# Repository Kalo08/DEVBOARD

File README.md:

# DEVBOARD

A custom devboard I made as a part of PROTOTYPE for HackClub.

Here are the parts I'm using,

1. USB-C port
2. Flash Memory
3. Crystal Oscillator
4. 1/0 Headers
5. RP2040
6. RGB Light
7. Custom Silk Screen

Rerouting, Adding details, and Ordering
I moved many of the routes to eliminate most of the warnings on my PCB and did extensive research on each error that appeared. I added a detail using the image converter, generated the Gerber and CSV files, uploaded them to JLCPCB, and started the ordering process. I had to change some parts because of what they had in stock, but my research says they should be equivalent.

-----------------------------------------------------------------------------------------------------------------------------------------------------------------------------------------------------------------------------------------------------------

Fixed the ts PCB and recreated it twice
Thanks to some hard drive issues, my KiCAD wasn't saving. So I re-created the whole thing, turned off my PC, then the next day logged on to finish it, and it was gone AGAIN! I replaced my hard drive, and KiCAD is working now. Thanks to that, I finally finished creating this PCB, and there aren't any errors. Now I get to add art to it!

With this newest iteration, I moved and changed many components after redoing this project twice, so I could route it as quickly as possible. It's safe to say I'm comfortable with KiCAD after this wholeexperiencee

-----------------------------------------------------------------------------------------------------------------------------------------------------------------------------------------------------------------------------------------------------------

created and routed the PCB
I placed all the electronics and routed them according to the schematic. Next, I'll test whether the PCB is functional and add art to it. I'll have to give it some thought, though. I've got some ideas for the art I'll add. And of course, Hack Club is gonna be one of said things.

-----------------------------------------------------------------------------------------------------------------------------------------------------------------------------------------------------------------------------------------------------------

Created Schematic
Just finished creating the schematic for the Dev Board. I followed the guide step by step and reviewed it for the finished product. Now I'm ready to move on to creating the PCB. I'm starting to dread the routing part though...

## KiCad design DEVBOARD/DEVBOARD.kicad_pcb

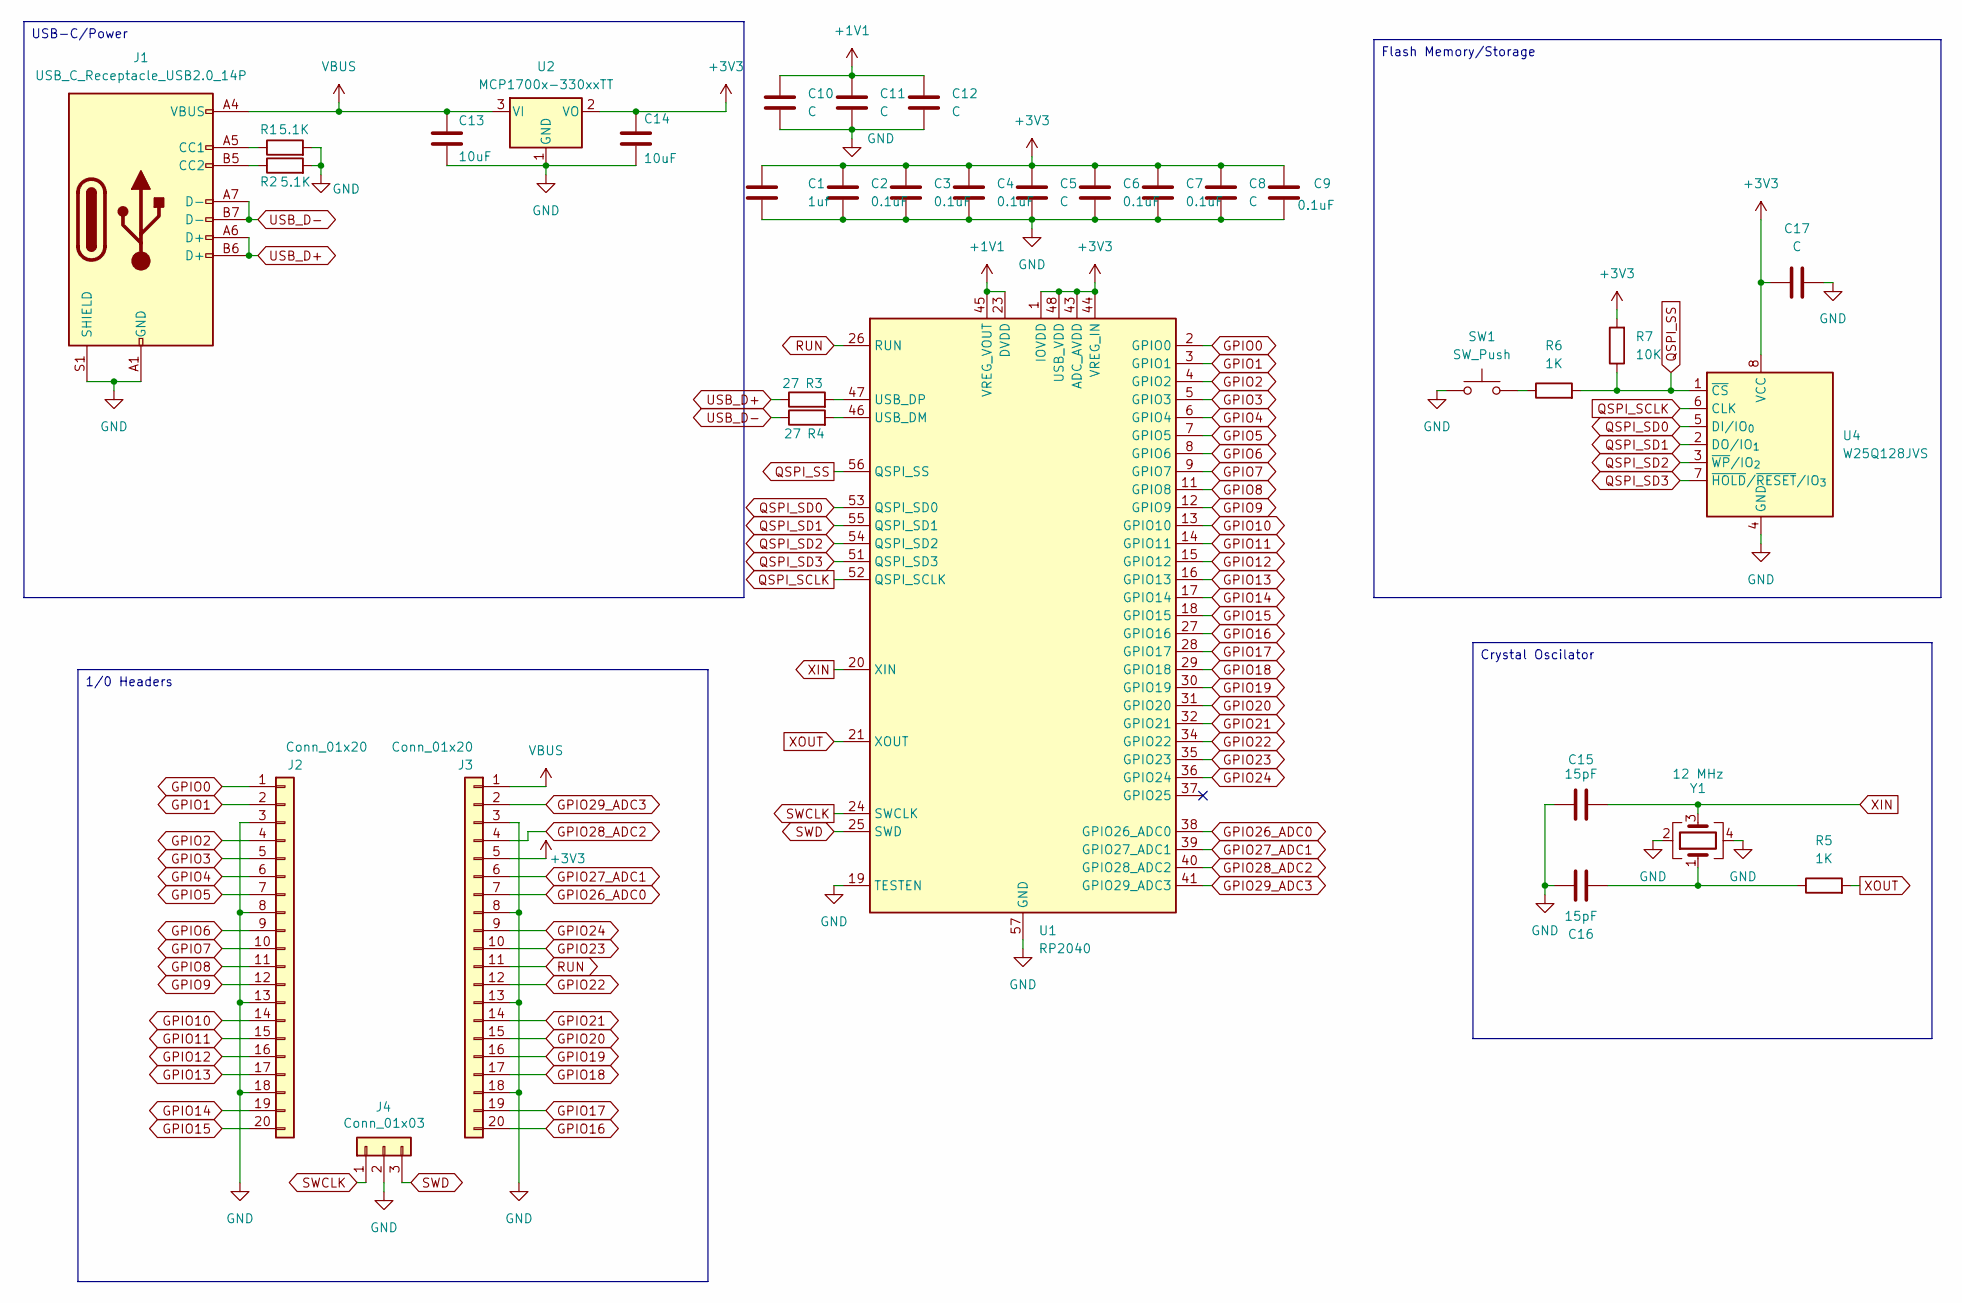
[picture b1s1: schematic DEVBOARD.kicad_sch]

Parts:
C1: 1uf; C_0402_1005Metric
C2, C3, C4, C6, C7, C9: 0.1uF; C_0402_1005Metric
C5, C8, C10, C11, C12, C17: C; C_0402_1005Metric
C13, C14: 10uF; C_0603_1608Metric
C15, C16: 15pF; C_0402_1005Metric
J1: USB_C_Receptacle_USB2.0_14P; USB_C_Receptacle_HRO_TYPE-C-31-M-12
J2, J3: Conn_01x20; PinHeader_1x20_P2.54mm_Vertical
J4: Conn_01x03; PinHeader_1x03_P2.54mm_Vertical
R1, R2: 5.1K; R_0402_1005Metric
R3, R4: 27; R_0402_1005Metric
R5, R6: 1K; R_0402_1005Metric
R7: 10K; R_0402_1005Metric
SW1: SW_Push; SW_Push_SPST_NO_Alps_SKRK
U1: RP2040; QFN-56-1EP_7x7mm_P0.4mm_EP3.2x3.2mm
U2: MCP1700x-330xxTT; SOT-23
U4: W25Q128JVS; Winbond_USON-8-1EP_3x2mm_P0.5mm_EP0.2x1.6mm
Y1: 12 MHz; Crystal_SMD_3225-4Pin_3.2x2.5mm

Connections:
+1V1: C10.1, C11.1, C12.1, U1.23 (DVDD), U1.45 (VREG_VOUT), U1.50 (DVDD)
+3V3: C1.1, C2.1, C3.1, C4.1, C5.1, C6.1, C7.1, C8.1, C9.1, C14.1, C17.1, J3.5, R7.2, U1.1 (IOVDD), U1.10 (IOVDD), U1.22 (IOVDD), U1.33 (IOVDD), U1.42 (IOVDD), U1.43 (ADC_AVDD), U1.44 (VREG_IN), U1.48 (USB_VDD), U1.49 (IOVDD), U2.2 (VO), U4.8 (VCC)
GND: C1.2, C2.2, C3.2, C4.2, C5.2, C6.2, C7.2, C8.2, C9.2, C10.2, C11.2, C12.2, C13.2, C14.2, C15.1, C16.1, C17.2, J1.A1 (GND), J1.A12 (GND), J1.B1 (GND), J1.B12 (GND), J1.S1 (SHIELD), J2.3, J2.8, J2.13, J2.18, J3.3, J3.8, J3.13, J3.18, J4.2, R1.2, R2.2, SW1.1, U1.19 (TESTEN), U1.57 (GND), U2.1 (GND), U4.4 (GND), Y1.2, Y1.4
GPIO0: J2.1, U1.2 (GPIO0)
GPIO1: J2.2, U1.3 (GPIO1)
GPIO2: J2.4, U1.4 (GPIO2)
GPIO3: J2.5, U1.5 (GPIO3)
GPIO4: J2.6, U1.6 (GPIO4)
GPIO5: J2.7, U1.7 (GPIO5)
GPIO6: J2.9, U1.8 (GPIO6)
GPIO7: J2.10, U1.9 (GPIO7)
GPIO8: J2.11, U1.11 (GPIO8)
GPIO9: J2.12, U1.12 (GPIO9)
GPIO10: J2.14, U1.13 (GPIO10)
GPIO11: J2.15, U1.14 (GPIO11)
GPIO12: J2.16, U1.15 (GPIO12)
GPIO13: J2.17, U1.16 (GPIO13)
GPIO14: J2.19, U1.17 (GPIO14)
GPIO15: J2.20, U1.18 (GPIO15)
GPIO16: J3.20, U1.27 (GPIO16)
GPIO17: J3.19, U1.28 (GPIO17)
GPIO18: J3.17, U1.29 (GPIO18)
GPIO19: J3.16, U1.30 (GPIO19)
GPIO20: J3.15, U1.31 (GPIO20)
GPIO21: J3.14, U1.32 (GPIO21)
GPIO22: J3.12, U1.34 (GPIO22)
GPIO23: J3.10, U1.35 (GPIO23)
GPIO24: J3.9, U1.36 (GPIO24)
GPIO26_ADC0: J3.7, U1.38 (GPIO26_ADC0)
GPIO27_ADC1: J3.6, U1.39 (GPIO27_ADC1)
GPIO28_ADC2: J3.4, U1.40 (GPIO28_ADC2)
GPIO29_ADC3: J3.2, U1.41 (GPIO29_ADC3)
unnamed: C16.2, R5.1, Y1.1
unnamed: J1.A5 (CC1), R1.1
unnamed: J1.B5 (CC2), R2.1
unnamed: R6.1, SW1.2
unnamed: R4.2, U1.46 (USB_DM)
unnamed: R3.2, U1.47 (USB_DP)
QSPI_SCLK: U1.52 (QSPI_SCLK), U4.6 (CLK)
QSPI_SD0: U1.53 (QSPI_SD0), U4.5 (DI/IO_{0})
QSPI_SD1: U1.55 (QSPI_SD1), U4.2 (DO/IO_{1})
QSPI_SD2: U1.54 (QSPI_SD2), U4.3 (~WP/IO_{2})
QSPI_SD3: U1.51 (QSPI_SD3), U4.7 (~HOLD/~RESET/IO_{3})
QSPI_SS: R6.2, R7.1, U1.56 (QSPI_SS), U4.1 (~CS)
RUN: J3.11, U1.26 (RUN)
SWCLK: J4.1, U1.24 (SWCLK)
SWD: J4.3, U1.25 (SWD)
USB_D+: J1.A6 (D+), J1.B6 (D+), R3.1
USB_D-: J1.A7 (D-), J1.B7 (D-), R4.1
VBUS: C13.1, J1.A4 (VBUS), J1.A9 (VBUS), J1.B4 (VBUS), J1.B9 (VBUS), J3.1, U2.3 (VI)
XIN: C15.2, U1.20 (XIN), Y1.3
XOUT: R5.2, U1.21 (XOUT)

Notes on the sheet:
1/0 Headers
USB-C/Power
Crystal Oscilator
Flash Memory/Storage

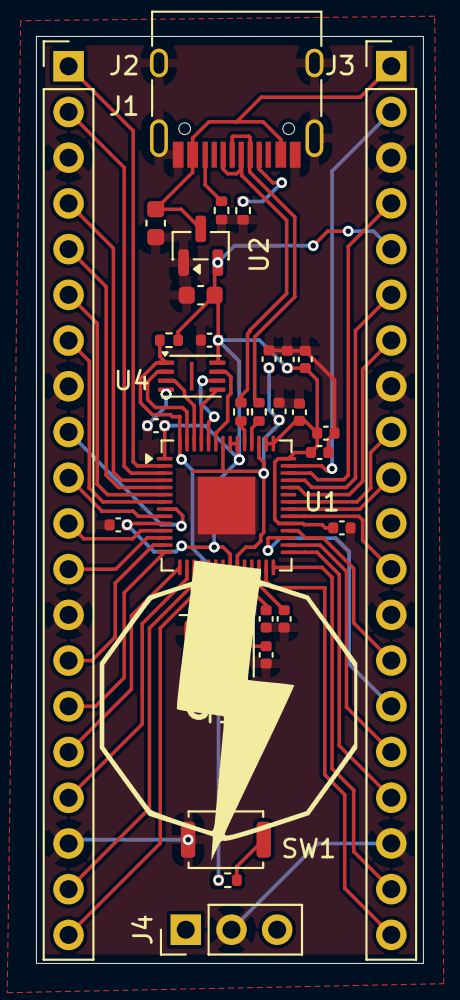
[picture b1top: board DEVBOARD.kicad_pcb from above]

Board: 2 copper layers, 21.5 x 51.5 mm, 33 parts (0 on the bottom side), 52 nets.

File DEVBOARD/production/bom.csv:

Designator,Footprint,Quantity,Value,LCSC Part #
C1,0402,1,1uf,
"C10, C11, C12, C17, C5, C8",0402,6,C,
"C13, C14",0603,2,10uF,
"C15, C16",0402,2,15pF,
"C2, C3, C4, C6, C7, C9",0402,6,0.1uF,
J1,USB_C_Receptacle_HRO_TYPE-C-31-M-12,1,USB_C_Receptacle_USB2.0_14P,
"J2, J3",PinHeader_1x20_P2.54mm_Vertical,2,Conn_01x20,
J4,PinHeader_1x03_P2.54mm_Vertical,1,Conn_01x03,
"R1, R2",0402,2,5.1K,
"R3, R4",0402,2,27,
"R5, R6",0402,2,1K,
R7,0402,1,10K,
SW1,SW_Push_SPST_NO_Alps_SKRK,1,SW_Push,
U1,QFN-56-1EP_7x7mm_P0.4mm_EP3.2x3.2mm,1,RP2040,
U2,SOT-23,1,MCP1700x-330xxTT,
U4,Winbond_USON-8-1EP_3x2mm_P0.5mm_EP0.2x1.6mm,1,W25Q128JVS,
Y1,Crystal_SMD_3225-4Pin_3.2x2.5mm,1,12 MHz,
